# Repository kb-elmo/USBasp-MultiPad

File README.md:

# USBasp MultiPad

[![CC BY-SA 4.0][cc-by-sa-shield]][cc-by-sa]

### USBasp flasher for Atmega32a and Atmega328p

### Partslist
Most of the parts in this list are just examples and they can be replaced with any component with the same specs.  
They don't have to be from any specific manufacturer or brand to work on this board.

|Count|Part|Designator|Octopart URL|
|-|-|-|-|
|1|ATmega8-16pu 28-pin DIP|U1|[Atmega8-16pu](https://octopart.com/atmega8-16pu-microchip-77760540)|
|1|28 pin DIP socket (optional but highly recommended)|U1|[TE Connectivity 1-2199298-9](https://octopart.com/1-2199298-9-te+connectivity-39188588)|
|1|2x5 pin header 2.54mm (optional)|AVR|[Würth 61201021621](https://octopart.com/61201021621-w%C3%BCrth+elektronik-8917783)|
|1|USB Type-B receptacle|USB1|[Molex 67068-8000](https://octopart.com/67068-8000-molex-314304)|
|1|500 mA polyfuse|F1|[Bourns MF-R050](https://octopart.com/mf-r050-bourns-19418)|
|1|12 MHz quarz crystal|X1|[CTS ATS120](https://octopart.com/ats120-cts+components-315826)|
|1|16 MHz quarz crystal|X2|[CTS ATS160](https://octopart.com/ats160-cts+components-315830)|
|1|4.7 uF electrolytic capacitor|C1|[Panasonic ECA-1HM4R7I](https://octopart.com/eca-1hm4r7i-panasonic-39478610)|
|2|100 nF ceramic disk capacitor|C2, C3|[Kemet C315C104M5U5TA](https://octopart.com/c315c104m5u5ta-kemet-83288)|
|4|22 pF ceramic disk capacitor|C4, C5, C6, C7|[Kemet C317C220J1G5TA](https://octopart.com/c317c220j1g5ta-kemet-1747641)|
|2|10 kΩ resistor|R2, R5|[Multicomp MF25 10k](https://octopart.com/mf25+10k-multicomp-2697429)|
|2|68 Ω resistor|R3, R4|[Multicomp MF25 68R](https://octopart.com/mf25+68r-multicomp-5364489)|
|3|1.5 kΩ resistor|R1, R6, R7|[Multicomp MF25 1k5](https://octopart.com/mf25+1k5-multicomp-5372506)|
|2|5mm LEDs|ACT, PWR|[Vishay TLHG5400](https://octopart.com/tlhg5400-vishay-39403037)|
|2|3.6 V zener diode (DO-35 BZX55C3V6)|D1, D2|[ON Semiconductor BZX85C3V6](https://octopart.com/bzx85c3v6-on+semiconductor-84409073)|
|1|40-pin ZIF socket (15.24mm row spacing)|U2|3M Textool 240-3345 (or equivalent)|
|1|28-pin ZIF socket (7.62mm row spacing)|U3|3M Textool 228-3341 (or equivalent)|

### PCB preview

This work is licensed under a
[Creative Commons Attribution-ShareAlike 4.0 International License][cc-by-sa].

[![CC BY-SA 4.0][cc-by-sa-image]][cc-by-sa]

[cc-by-sa]: http://creativecommons.org/licenses/by-sa/4.0/
[cc-by-sa-image]: https://licensebuttons.net/l/by-sa/4.0/88x31.png
[cc-by-sa-shield]: https://img.shields.io/badge/License-CC%20BY--SA%204.0-lightgrey.svg

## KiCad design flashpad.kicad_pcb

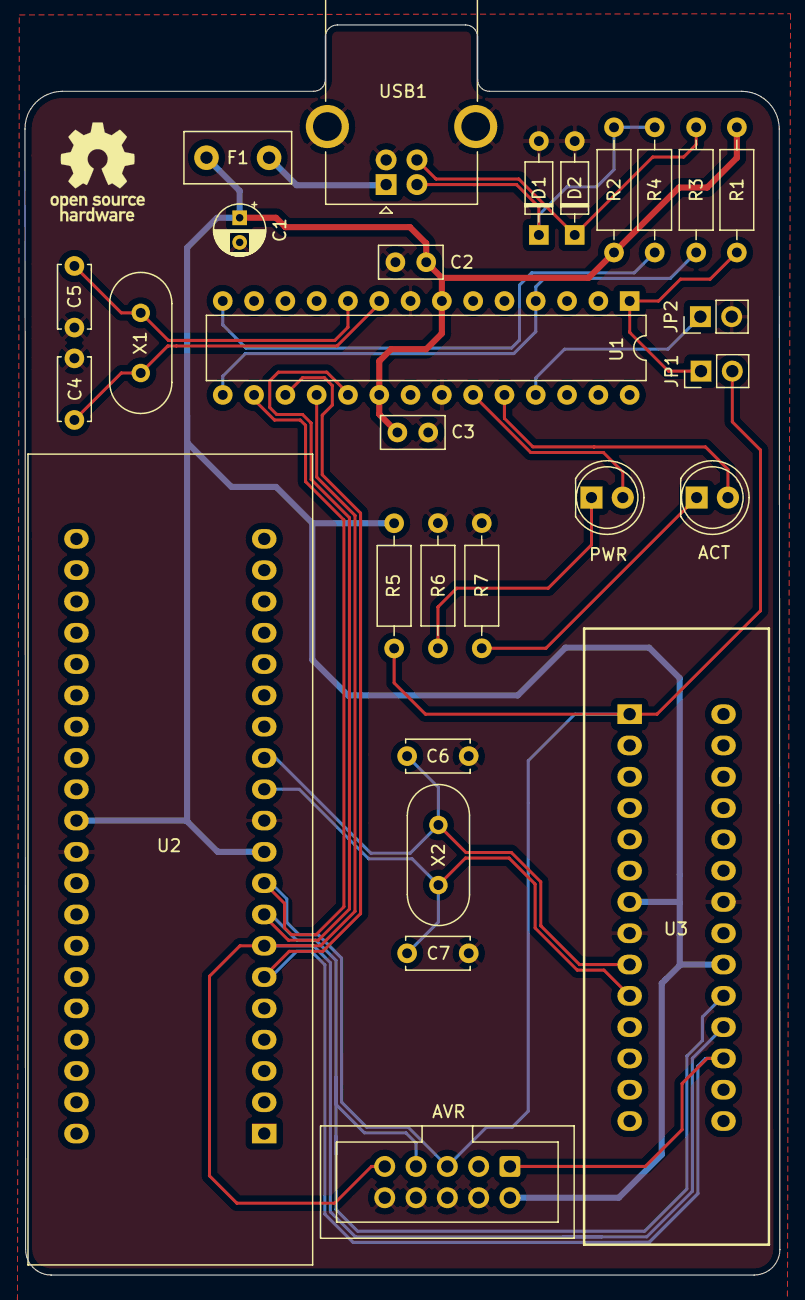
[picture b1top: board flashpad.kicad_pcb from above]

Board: 2 copper layers, 61.3 x 101.4 mm, 28 parts (0 on the bottom side), 21 nets.

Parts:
ACT: LED; LED_D5.0mm
AVR: AVR-ISP-10; IDC-Header_2x05_P2.54mm_Vertical
C1: 4.7u; CP_Radial_D4.0mm_P2.00mm
C2, C3: 100n; C_Disc_D5.0mm_W2.5mm_P2.50mm
C4, C5, C6, C7: 22p; C_Disc_D5.0mm_W2.5mm_P5.00mm
D1, D2: 3.6V; D_DO-35_SOD27_P7.62mm_Horizontal
F1: Polyfuse; Fuse_Littelfuse_395Series
JP1: SelfProg; PinHeader_1x02_P2.54mm_Vertical
JP2: SlowSCK; PinHeader_1x02_P2.54mm_Vertical
PWR: LED; LED_D5.0mm
R1, R5: 10k; R_Axial_DIN0207_L6.3mm_D2.5mm_P10.16mm_Horizontal
R2: 1.5k; R_Axial_DIN0207_L6.3mm_D2.5mm_P10.16mm_Horizontal
R3, R4: 68R; R_Axial_DIN0207_L6.3mm_D2.5mm_P10.16mm_Horizontal
R6, R7: 1.5K; R_Axial_DIN0207_L6.3mm_D2.5mm_P10.16mm_Horizontal
U1: ATmega8A-PU; DIP-28_W7.62mm
U2: ATmega32A-PU; socket40dip
U3: ATmega328P-PU; socket28dip
USB1: USB_B; USB_B_OST_USB-B1HSxx_Horizontal
X1: 12Mhz; Crystal_HC49-4H_Vertical
X2: 16Mhz; Crystal_HC49-4H_Vertical

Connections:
+5V: AVR.2, C1.1, C2.1, C3.1, F1.1, R1.1, R2.1, R5.2, U1.7, U1.20, U2.10, U2.30, U3.7, U3.20
D+: R3.2, U1.4, U1.15
D-: R4.2, U1.14
GND: AVR.4, AVR.6, AVR.8, AVR.10, C1.2, C2.2, C3.2, C4.2, C5.2, C6.2, C7.2, D1.2, D2.2, JP2.2, R6.1, R7.1, U1.8, U1.22, U2.11, U2.31, U3.8, U3.22, USB1.4, USB1.5
LED1: PWR.2, U1.23
LED2: ACT.2, U1.24
MISO: AVR.9, U1.18, U2.7, U3.18
MOSI: AVR.1, U1.17, U2.6, U3.17
unnamed: D1.1, R2.2, R4.1, USB1.2
unnamed: D2.1, R3.1, USB1.3
unnamed: JP1.1, R1.2, U1.1
unnamed: JP2.1, U1.25
unnamed: PWR.1, R6.2
unnamed: ACT.1, R7.2
RESET: AVR.5, JP1.2, R5.1, U1.16, U2.9, U3.1
SCK: AVR.7, U1.19, U2.8, U3.19
VCC: F1.2, USB1.1
XTAL1_1: C4.1, U1.9, X1.1
XTAL1_2: C5.1, U1.10, X1.2
XTAL2_1: C6.1, U2.13, U3.9, X2.1
XTAL2_2: C7.1, U2.12, U3.10, X2.2

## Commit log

2021-05-04 rev2
2021-05-07 add readme
2021-05-20 fix footprints
2021-05-20 Update LICENSE
2021-05-29 fix prototype issues
2021-06-09 added firmware
2021-08-16 change license
